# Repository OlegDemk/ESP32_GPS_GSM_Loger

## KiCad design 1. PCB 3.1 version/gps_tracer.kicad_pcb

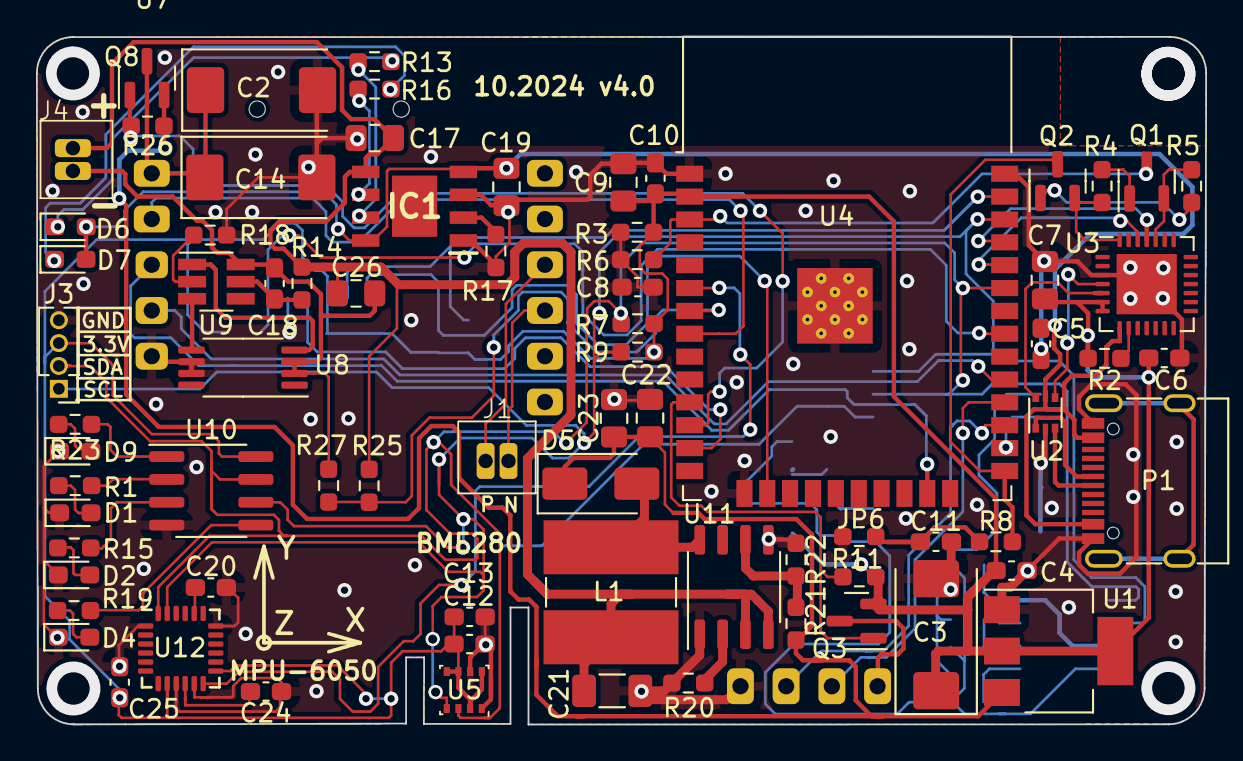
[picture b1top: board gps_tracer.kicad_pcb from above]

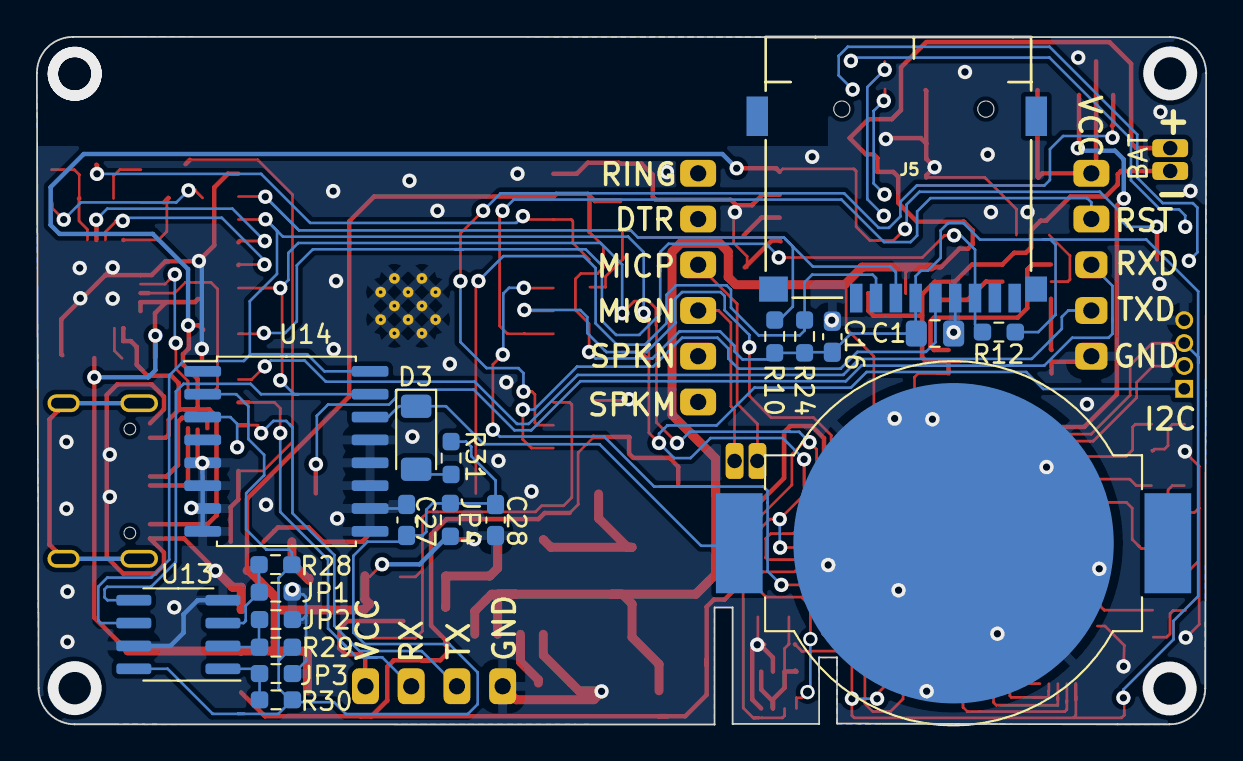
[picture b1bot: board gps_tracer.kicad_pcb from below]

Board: 2 copper layers, 65.0 x 38.2 mm, 98 parts (20 on the bottom side), 68 nets.

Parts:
AE1: Antenna; GPS_ANTENNA
BT1: Battery_Cell; BatteryHolder_MPD_BC2003_1x2032
C1, C9, C22, C23, C26: 22u; C_0805_2012Metric_Pad1.18x1.45mm_HandSolder
C2, C3, C14: 470u; CP_EIA-7343-31_Kemet-D
C4, C5, C6, C8, C10, C11, C12, C13, C20, C24, C25, C28: 100n; C_0603_1608Metric_Pad1.08x0.95mm_HandSolder
C7: 47u; C_0805_2012Metric_Pad1.18x1.45mm_HandSolder
C16, C18: 100nF; C_0603_1608Metric_Pad1.08x0.95mm_HandSolder
C17, C19: 16uF; C_0805_2012Metric_Pad1.18x1.45mm_HandSolder
C21: 100u; C_1206_3216Metric_Pad1.33x1.80mm_HandSolder
C27: 1u; C_0603_1608Metric_Pad1.08x0.95mm_HandSolder
D1: GREEN LED; LED_0603_1608Metric_Pad1.05x0.95mm_HandSolder
D2: BLUE LED; LED_0603_1608Metric_Pad1.05x0.95mm_HandSolder
D3: 1N914WT; D_MiniMELF
D4: YELLOW_LED; LED_0603_1608Metric_Pad1.05x0.95mm_HandSolder
D5: SS14; D_SMA
D6: LED Charging red; LED_0603_1608Metric_Pad1.05x0.95mm_HandSolder
D7: LED Full blue; LED_0603_1608Metric_Pad1.05x0.95mm_HandSolder
D9: RED LED; LED_0603_1608Metric_Pad1.05x0.95mm_HandSolder
IC1: TC4056A; SOIC127P600X175-9N
J1: Mic; JST 1.25
J3: I2C; PinHeader_1x04_P1.27mm_Vertical
J4: BATTERY; JST 1.25
J5: Micro_SD_Card; J_SD_Card-micro_socket_A (1)
JP1: A2; R_0603_1608Metric_Pad0.98x0.95mm_HandSolder
JP2: A1; R_0603_1608Metric_Pad0.98x0.95mm_HandSolder
JP3: A0; R_0603_1608Metric_Pad0.98x0.95mm_HandSolder
JP4: RTC ON R0 0603; R_0603_1608Metric_Pad0.98x0.95mm_HandSolder
JP6: BOOT; R_0603_1608Metric_Pad0.98x0.95mm_HandSolder
L1: 3.3uH; L_Ferrocore_DLG-0703
P1: USB_C_Plug_USB2.0; USB_C_Receptacle_G-Switch_GT-USB-7010ASV
Q1, Q2: S8050; SOT-23
Q3, Q8: FDN358P; SOT-23
R1, R15, R19, R23: 700; R_0603_1608Metric_Pad0.98x0.95mm_HandSolder
R2: 2k; R_0603_1608Metric_Pad0.98x0.95mm_HandSolder
R3, R4, R5, R10, R12, R22, R24: 10k; R_0603_1608Metric_Pad0.98x0.95mm_HandSolder
R6, R8: 470; R_0603_1608Metric_Pad0.98x0.95mm_HandSolder
R7, R9, R28, R29, R30: 4.7k; R_0603_1608Metric_Pad0.98x0.95mm_HandSolder
R11, R26: 9k; R_0603_1608Metric_Pad0.98x0.95mm_HandSolder
R13, R16, R18: 1k; R_0603_1608Metric_Pad0.98x0.95mm_HandSolder
R14: 100; R_0603_1608Metric_Pad0.98x0.95mm_HandSolder
R17: 1200; R_0603_1608Metric_Pad0.98x0.95mm_HandSolder
R20: 30k; R_0603_1608Metric_Pad0.98x0.95mm_HandSolder
R21: 62k; R_0603_1608Metric_Pad0.98x0.95mm_HandSolder
R25, R27: ????; R_0603_1608Metric_Pad0.98x0.95mm_HandSolder
R31: 200; R_0603_1608Metric_Pad0.98x0.95mm_HandSolder
U1: AMS1117-3.3; SOT-223-3_TabPin2
U2: USBLC6-2P6; SOT-666
U3: CP2102N-Axx-xQFN28; QFN-28-1EP_5x5mm_P0.5mm_EP3.35x3.35mm
U4: ESP32-WROOM-32
U5: BME280; Bosch_LGA-8_2.5x2.5mm_P0.65mm_ClockwisePinNumbering
U6: GY_GPS6MV2_module
U7: SIM800L-CORE
U8: FS8205A; TSSOP-8_4.4x3mm_P0.65mm
U9: DW01A; SOT-23-6_Handsoldering
U10: PCA9536D; SOIC-8_3.9x4.9mm_P1.27mm
U11: FP6298; SOP-8_3.9x4.9mm_P1.27mm
U12: MPU-6050; InvenSense_QFN-24_4x4mm_P0.5mm
U13: AT24CS02-SSHM; SOIC-8_3.9x4.9mm_P1.27mm
U14: DS3231M; SOIC-16W_7.5x10.3mm_P1.27mm

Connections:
+3.3V: C1.1, C3.1, C4.1, C6.1, C7.1, C9.1, C10.1, C12.1, C13.1, C16.1, C25.2, J3.3, J5.4 (VSS), JP4.2 (B), Q3.2 (S), R2.1, R3.1, R7.1, R9.1, R10.2, R11.2, R12.2, R24.2, U1.2 (VO), U3.6 (VDD), U3.7 (VREGIN), U4.2 (VDD), U5.2 (CSB), U5.5 (SDO), U5.6 (VDDIO), U5.8 (VDD), U10.8 (VDD), U12.8 (VLOGIC), U12.13 (VDD)
+5V: C5.1, C19.1, D6.2 (A), D7.2 (A), IC1.4 (VCC), IC1.8 (CE), P1.A4 (VBUS), P1.A9 (VBUS), P1.B4 (VBUS), P1.B9 (VBUS), U2.5 (VBUS), U3.8 (VBUS)
BATTERY_VOLTAGE: R25.2, R27.1, U4.7 (IO35)
DTR: Q2.2 (E), R4.2, U3.28 (~DTR)
DTS: Q1.2 (E), R5.2, U3.24 (~RTS)
EN: Q1.3 (C), R6.1, U4.3 (EN)
EXTERNAL_WOKE_UP: U4.26 (IO4), U14.3 (~INT/SQW)
GND: BT1.2 (-), C1.2, C2.2, C3.2, C4.2, C5.2, C6.2, C7.2, C8.1, C8.2, C9.2, C10.2, C11.2, C12.2, C13.2, C14.2, C16.2, C17.2, C19.2, C20.1, C21.2, C22.2, C23.2, C24.1, C25.1, C27.2, C28.2, D1.1 (K), D2.1 (K), D4.1 (K), D9.1 (K), IC1.1 (TEMP), IC1.3 (GND), J3.4, J5.6 (VDD), JP1.1 (A), JP2.1 (A), JP3.1 (A), JP6.2 (B), P1.A1 (GND), P1.A12 (GND), P1.B1 (GND), P1.B12 (GND), R3.2, R6.2, R17.1, R18.1, R20.1, R22.1, U1.1 (GND), U2.2 (GND), U3.3 (GND), U3.29 (GND), U4.1 (GND), U4.15 (GND), U4.38 (GND), U4.39 (GND), U5.1 (GND), U5.7 (GND), U6.4 (GND), U7.5 (GND), U8.6 (S2), U8.7 (S2), U10.4 (VSS), U11.1 (PGND), U11.5 (GND), U12.1 (CLKIN), U12.9 (AD0), U12.11 (FSYNC), U12.18 (GND), U13.4 (GND), U13.7 (WP), U14.5 (GND), U14.6 (GND), U14.7 (GND), U14.8 (GND), U14.9 (GND), U14.10 (GND), U14.11 (GND), U14.12 (GND), U14.13 (GND)
GPS_RX: U4.28 (IO17), U6.2 (RX)
GPS_TX: U4.27 (IO16), U6.3 (TX)
GSM_POWER_SOURSE: C22.1, C23.1, D5.1 (K), Q8.2 (S), R21.2, R26.2, U1.3 (VI)
IO0: Q2.3 (C), R8.2, U4.25 (IO0)
MICROSD_CLK: J5.5 (CLK), U4.13 (IO14)
MICROSD_CS: J5.2 (DAT1), R24.1, U4.16 (IO13)
MICROSD_MISO: J5.7 (CMD), R12.1, U4.31 (IO19)
MICROSD_MOSI: J5.3 (DAT0), R10.1, U4.37 (IO23)
MPU5060_INT: U4.6 (IO34), U12.12 (INT)
unnamed: BT1.1 (+), D3.1 (K), U14.14 (VBAT)
unnamed: D1.2 (A), R1.2
unnamed: D2.2 (A), R15.2
unnamed: D3.2 (A), R31.1
unnamed: D4.2 (A), R19.2
unnamed: D5.2 (A), L1.2, U11.8 (LX)
unnamed: D6.1 (K), R13.2
unnamed: D7.1 (K), R16.2
unnamed: D9.2 (A), R23.2
unnamed: C17.1, C21.1, C26.1, IC1.5 (BAT), J4.2, L1.1, R14.1, R25.1, U11.3 (Vcc), U11.4 (EN)
unnamed: IC1.7 (CHRG), R13.1
unnamed: IC1.2 (PROG), R17.2
unnamed: IC1.6 (STDBY), R16.1
unnamed: J1.1, U7.8 (MICN)
unnamed: J1.2, U7.9 (MICP)
unnamed: C18.2, C26.2, J4.1, R27.2, U8.2 (S1), U8.3 (S1), U9.6 (GND)
unnamed: JP1.2 (B), R28.2, U13.3 (A2)
unnamed: JP2.2 (B), R29.2, U13.2 (A1)
unnamed: JP3.2 (B), R30.2, U13.1 (A0)
unnamed: C27.1, C28.1, JP4.1 (A), R28.1, R29.1, R30.1, R31.2, U13.8 (VCC), U14.2 (VCC)
unnamed: C11.1, JP6.1 (A), R8.1
unnamed: P1.A6 (D+), U2.3 (I/O2)
unnamed: P1.A7 (D-), U2.1 (I/O1)
unnamed: Q1.1 (B), R4.1
unnamed: Q2.1 (B), R5.1
unnamed: Q3.3 (D), U6.1 (VCC)
unnamed: C2.1, C14.1, Q8.3 (D), U7.1 (VCC)
unnamed: U2.4 (I/O2), U3.4 (D+)
unnamed: U2.6 (I/O1), U3.5 (D-)
unnamed: R2.2, U3.9 (~RST)
unnamed: R18.2, U9.2 (CS)
unnamed: C18.1, R14.2, U9.5 (VCC)
unnamed: R23.1, U10.1 (IO0)
unnamed: R1.1, U10.2 (IO1)
unnamed: R15.1, U10.3 (IO2)
unnamed: R19.1, U10.5 (IO3)
unnamed: R21.1, R22.2, U11.6 (FB)
unnamed: R20.2, U11.2 (OC)
unnamed: C20.2, U12.20 (CPOUT)
unnamed: C24.2, U12.10 (REGOUT)
OC: U8.5 (G2), U9.3 (OC)
OD: U8.4 (G1), U9.1 (OD)
POWER_OF_GPS: Q3.1 (G), R11.1, U4.11 (IO26)
POWER_OF_GSM: Q8.1 (G), R26.1, U4.12 (IO27)
RST_GSM: U4.8 (IO32), U7.2 (RST)
RXD: U3.26 (TXD), U4.34 (RXD0/IO3)
RXD_GSM: U4.23 (IO15), U7.3 (RXD)
SCL: J3.1, R9.2, U4.36 (IO22), U5.4 (SCK), U10.6 (SCL), U12.23 (SCL), U13.6 (SCL), U14.16 (SCL)
SDA: J3.2, R7.2, U4.33 (IO21), U5.3 (SDI), U10.7 (SDA), U12.24 (SDA), U13.5 (SDA), U14.15 (SDA)
TXD: U3.25 (RXD), U4.35 (TXD0/IO1)
TXD_GSM: U4.29 (IO5), U7.4 (TXD)

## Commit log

2024-09-05 Log GPS data into Micro CD card in .kml file, for https://earth.google.com/
2024-09-05 refactoring and optimisation code
2024-09-06 finiched work with GPS loging into file
2024-09-13 SIM800l receive and send sms, and answer on call my number
2024-09-20 GSM code has some bugs
2024-09-22 diagram file updated
2024-09-23 BUG was fixed
2024-10-02 BUG with SMS was fixed
2024-10-02 simple HTTP server was added
2024-10-03 http server was testet with all project
2024-10-22 HTTP file server added into /Parts project/6. Web server/13. HTTP file server. The files in Micro SD card can be deleted or download from browser
